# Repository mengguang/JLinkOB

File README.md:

# JLinkOB
I know nothing about this project.

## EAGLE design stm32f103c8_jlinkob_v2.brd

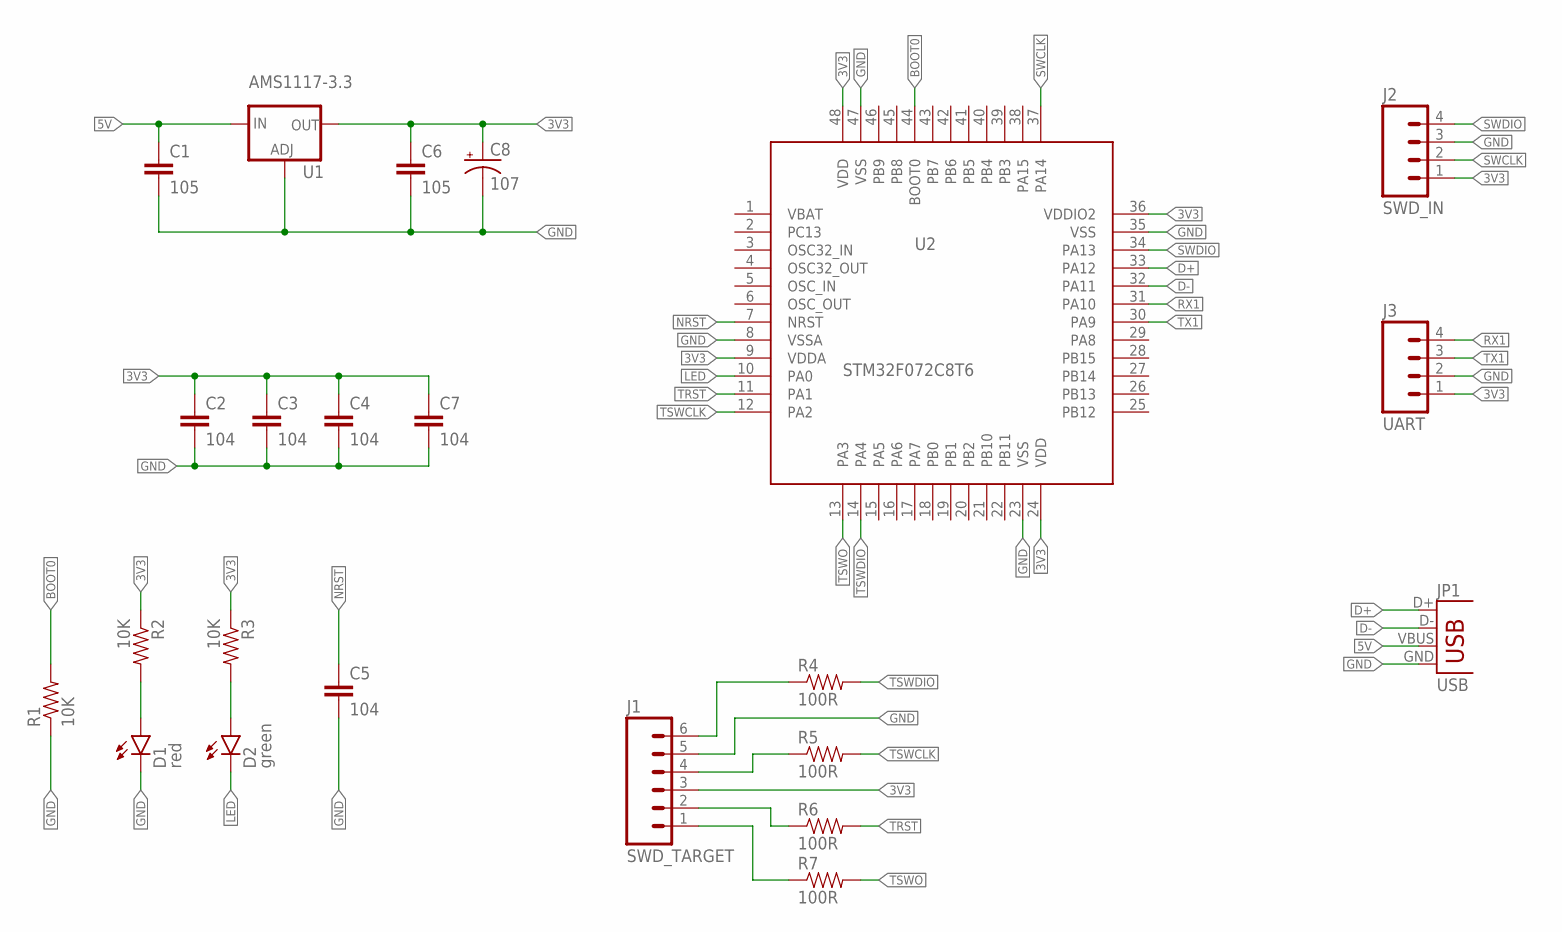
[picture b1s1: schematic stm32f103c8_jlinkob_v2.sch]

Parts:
C1, C6: 105; 0603-CAP
C2, C3, C4, C5, C7: 104; 0603-CAP
C8: 107; EIA3528
D1: red; LED-0603-SEEED
D2: green; LED-0603-SEEED
J1: SWD_TARGET; 1X06_NO_SILK
J2: SWD_IN; 1X04_NO_SILK
J3: UART; 1X04_NO_SILK
JP1: USB; MICROUSB-U-F-M5DD-Y-1
R1, R2, R3: 10K; 0603-RES
R4, R5, R6, R7: 100R; 0603-RES
U1: AMS1117-3.3; SOT223
U2: STM32F072C8T6; LQFP-48

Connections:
3V3: C2.1, C3.1, C4.1, C6.1, C7.1, C8.A (+), J1.3, J2.1, J3.1, R2.1, R3.1, U1.2 (OUT), U1.4 (OUT), U2.9 (VDDA), U2.24 (VDD), U2.36 (VDDIO2), U2.48 (VDD)
5V: C1.1, JP1.VBUS, U1.3 (IN)
BOOT0: R1.2, U2.44 (BOOT0)
D+: JP1.D+, U2.33 (PA12)
D-: JP1.D-, U2.32 (PA11)
GND: C1.2, C2.2, C3.2, C4.2, C5.2, C6.2, C7.2, C8.C (-), D1.- (C), J1.5, J2.3, J3.2, JP1.GND, R1.1, U1.1 (ADJ), U2.8 (VSSA), U2.23 (VSS), U2.35 (VSS), U2.47 (VSS)
LED: D2.- (C), U2.10 (PA0)
unnamed: D2.+ (A), R3.2
unnamed: J1.6, R4.1
unnamed: J1.4, R5.1
unnamed: D1.+ (A), R2.2
unnamed: J1.2, R6.1
unnamed: J1.1, R7.1
NRST: C5.1, U2.7 (NRST)
RX1: J3.4, U2.31 (PA10)
SWCLK: J2.2, U2.37 (PA14)
SWDIO: J2.4, U2.34 (PA13)
TRST: R6.2, U2.11 (PA1)
TSWCLK: R5.2, U2.12 (PA2)
TSWDIO: R4.2, U2.14 (PA4)
TSWO: R7.2, U2.13 (PA3)
TX1: J3.3, U2.30 (PA9)

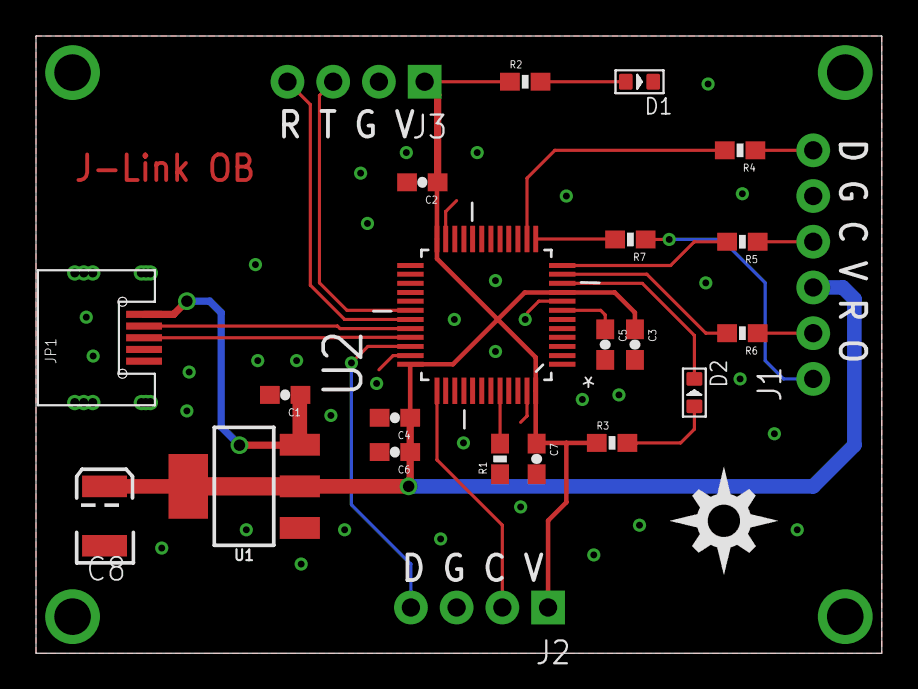
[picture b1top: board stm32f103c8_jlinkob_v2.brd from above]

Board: 2 copper layers, 47.0 x 34.3 mm, 24 parts (0 on the bottom side), 22 nets.

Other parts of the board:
U$1: DIYNOVA_LOGO

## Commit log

2020-07-01 change file name
2020-07-01 rename file

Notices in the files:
parts and their libraries:
SparkFun-Connectors: Licensing: Creative Commons ShareAlike 4.0 International - https://creativecommons.org/licenses/by-sa/4.0
